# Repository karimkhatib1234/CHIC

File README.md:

# CHIC
 Prototyping of the Canary
# CHIC

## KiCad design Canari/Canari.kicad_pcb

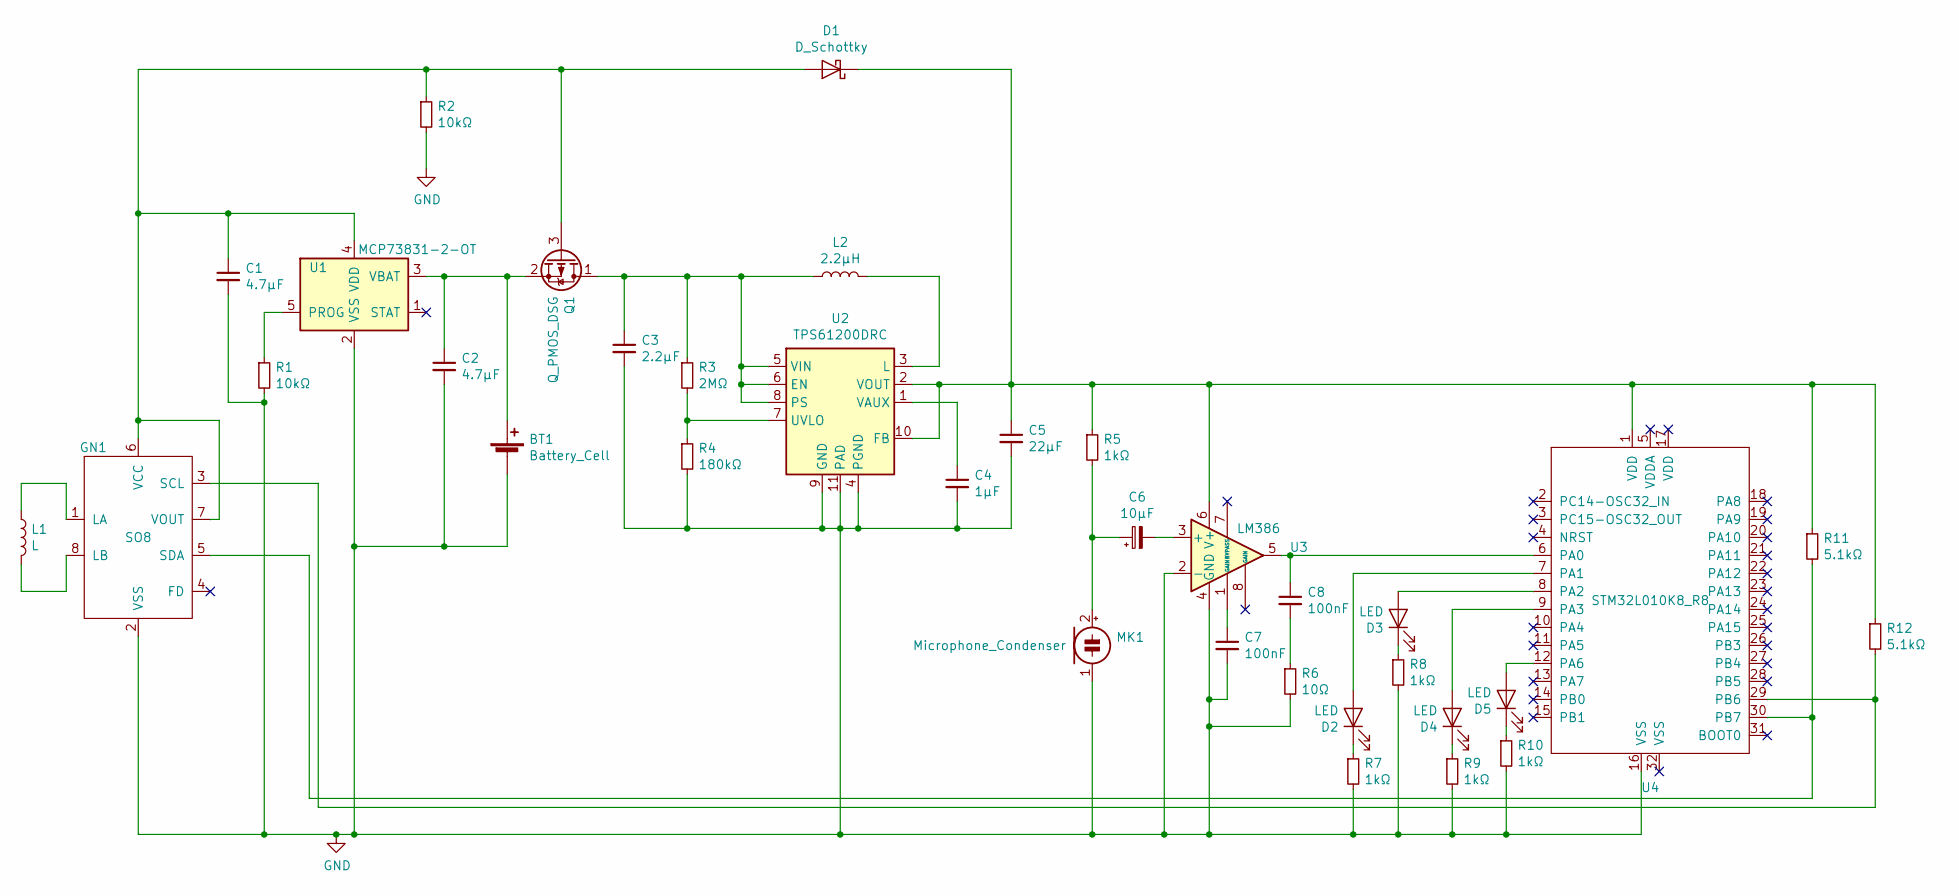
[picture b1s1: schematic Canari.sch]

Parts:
BT1: Battery_Cell; C_1812_4532Metric
C1, C2: 4.7µF; C_0402_1005Metric
C3: 2.2µF; C_0603_1608Metric
C4: 1µF; C_0603_1608Metric
C5: 22µF; C_0805_2012Metric
C6: 10µF; C_0805_2012Metric
C7, C8: 100nF; C_0402_1005Metric
D1: D_Schottky; STPS5L60S
D2, D3, D4, D5: LED; LED_3mm_Radial
GN1: SO8; SOT176-1
L1: L; Coil
L2: 2.2µH; L_0805_2012Metric
MK1: Microphone_Condenser; MIC_CMA-4544PF-W
Q1: Q_PMOS_DSG; SC-59
R1, R2: 10kΩ; R_0603_1608Metric
R3: 2MΩ; R_0402_1005Metric
R4: 180kΩ; R_0603_1608Metric
R5, R7, R8, R9, R10: 1kΩ; R_0603_1608Metric
R6: 10Ω; R_0402_1005Metric
R11, R12: 5.1kΩ; R_0402_1005Metric
U1: MCP73831-2-OT; SOT-23-5
U2: TPS61200DRC; Texas_S-PVSON-N10_ThermalVias
U3: LM386; SOIC-8_3.9x4.9mm_P1.27mm
U4: STM32L010K8_R8; LQFP-32_7x7mm

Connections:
GND: BT1.2 (-), C1.2, C2.2, C3.2, C4.2, C5.2, C7.2, GN1.2 (VSS), MK1.1 (-), R1.2, R2.2, R4.2, R6.2, R7.2, R8.2, R9.2, R10.2, U1.2 (VSS), U2.4 (PGND), U2.9 (GND), U2.11 (PAD), U3.2 (-), U3.4 (GND), U4.16 (VSS)
unnamed: BT1.1 (+), C2.1, Q1.2 (S), U1.3 (VBAT)
unnamed: C1.1, D1.2 (A), GN1.6 (VCC), GN1.7 (VOUT), Q1.3 (G), R2.1, U1.4 (VDD)
unnamed: C3.1, L2.1, Q1.1 (D), R3.1, U2.5 (VIN), U2.6 (EN), U2.8 (PS)
unnamed: C4.1, U2.1 (VAUX)
unnamed: C5.1, D1.1 (K), R5.1, R11.1, R12.1, U2.2 (VOUT), U2.10 (FB), U3.6 (V+), U4.1 (VDD)
unnamed: C6.1, MK1.2 (+), R5.2
unnamed: C6.2, U3.3 (+)
unnamed: C7.1, U3.1 (GAIN)
unnamed: C8.1, U3.5, U4.6 (PA0)
unnamed: C8.2, R6.1
unnamed: D2.1 (K), R7.1
unnamed: D2.2 (A), U4.7 (PA1)
unnamed: D3.1 (K), R8.1
unnamed: D3.2 (A), U4.8 (PA2)
unnamed: D4.1 (K), R9.1
unnamed: D4.2 (A), U4.9 (PA3)
unnamed: D5.1 (K), R10.1
unnamed: D5.2 (A), U4.12 (PA6)
unnamed: GN1.1 (LA), L1.1
unnamed: GN1.3 (SCL), R12.2, U4.29 (PB6)
unnamed: GN1.5 (SDA), R11.2, U4.30 (PB7)
unnamed: GN1.8 (LB), L1.2
unnamed: L2.2, U2.3 (L)
unnamed: R1.1, U1.5 (PROG)
unnamed: R3.2, R4.1, U2.7 (UVLO)

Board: 2 copper layers, 35 parts (30 on the bottom side), 26 nets, no tracks yet.
